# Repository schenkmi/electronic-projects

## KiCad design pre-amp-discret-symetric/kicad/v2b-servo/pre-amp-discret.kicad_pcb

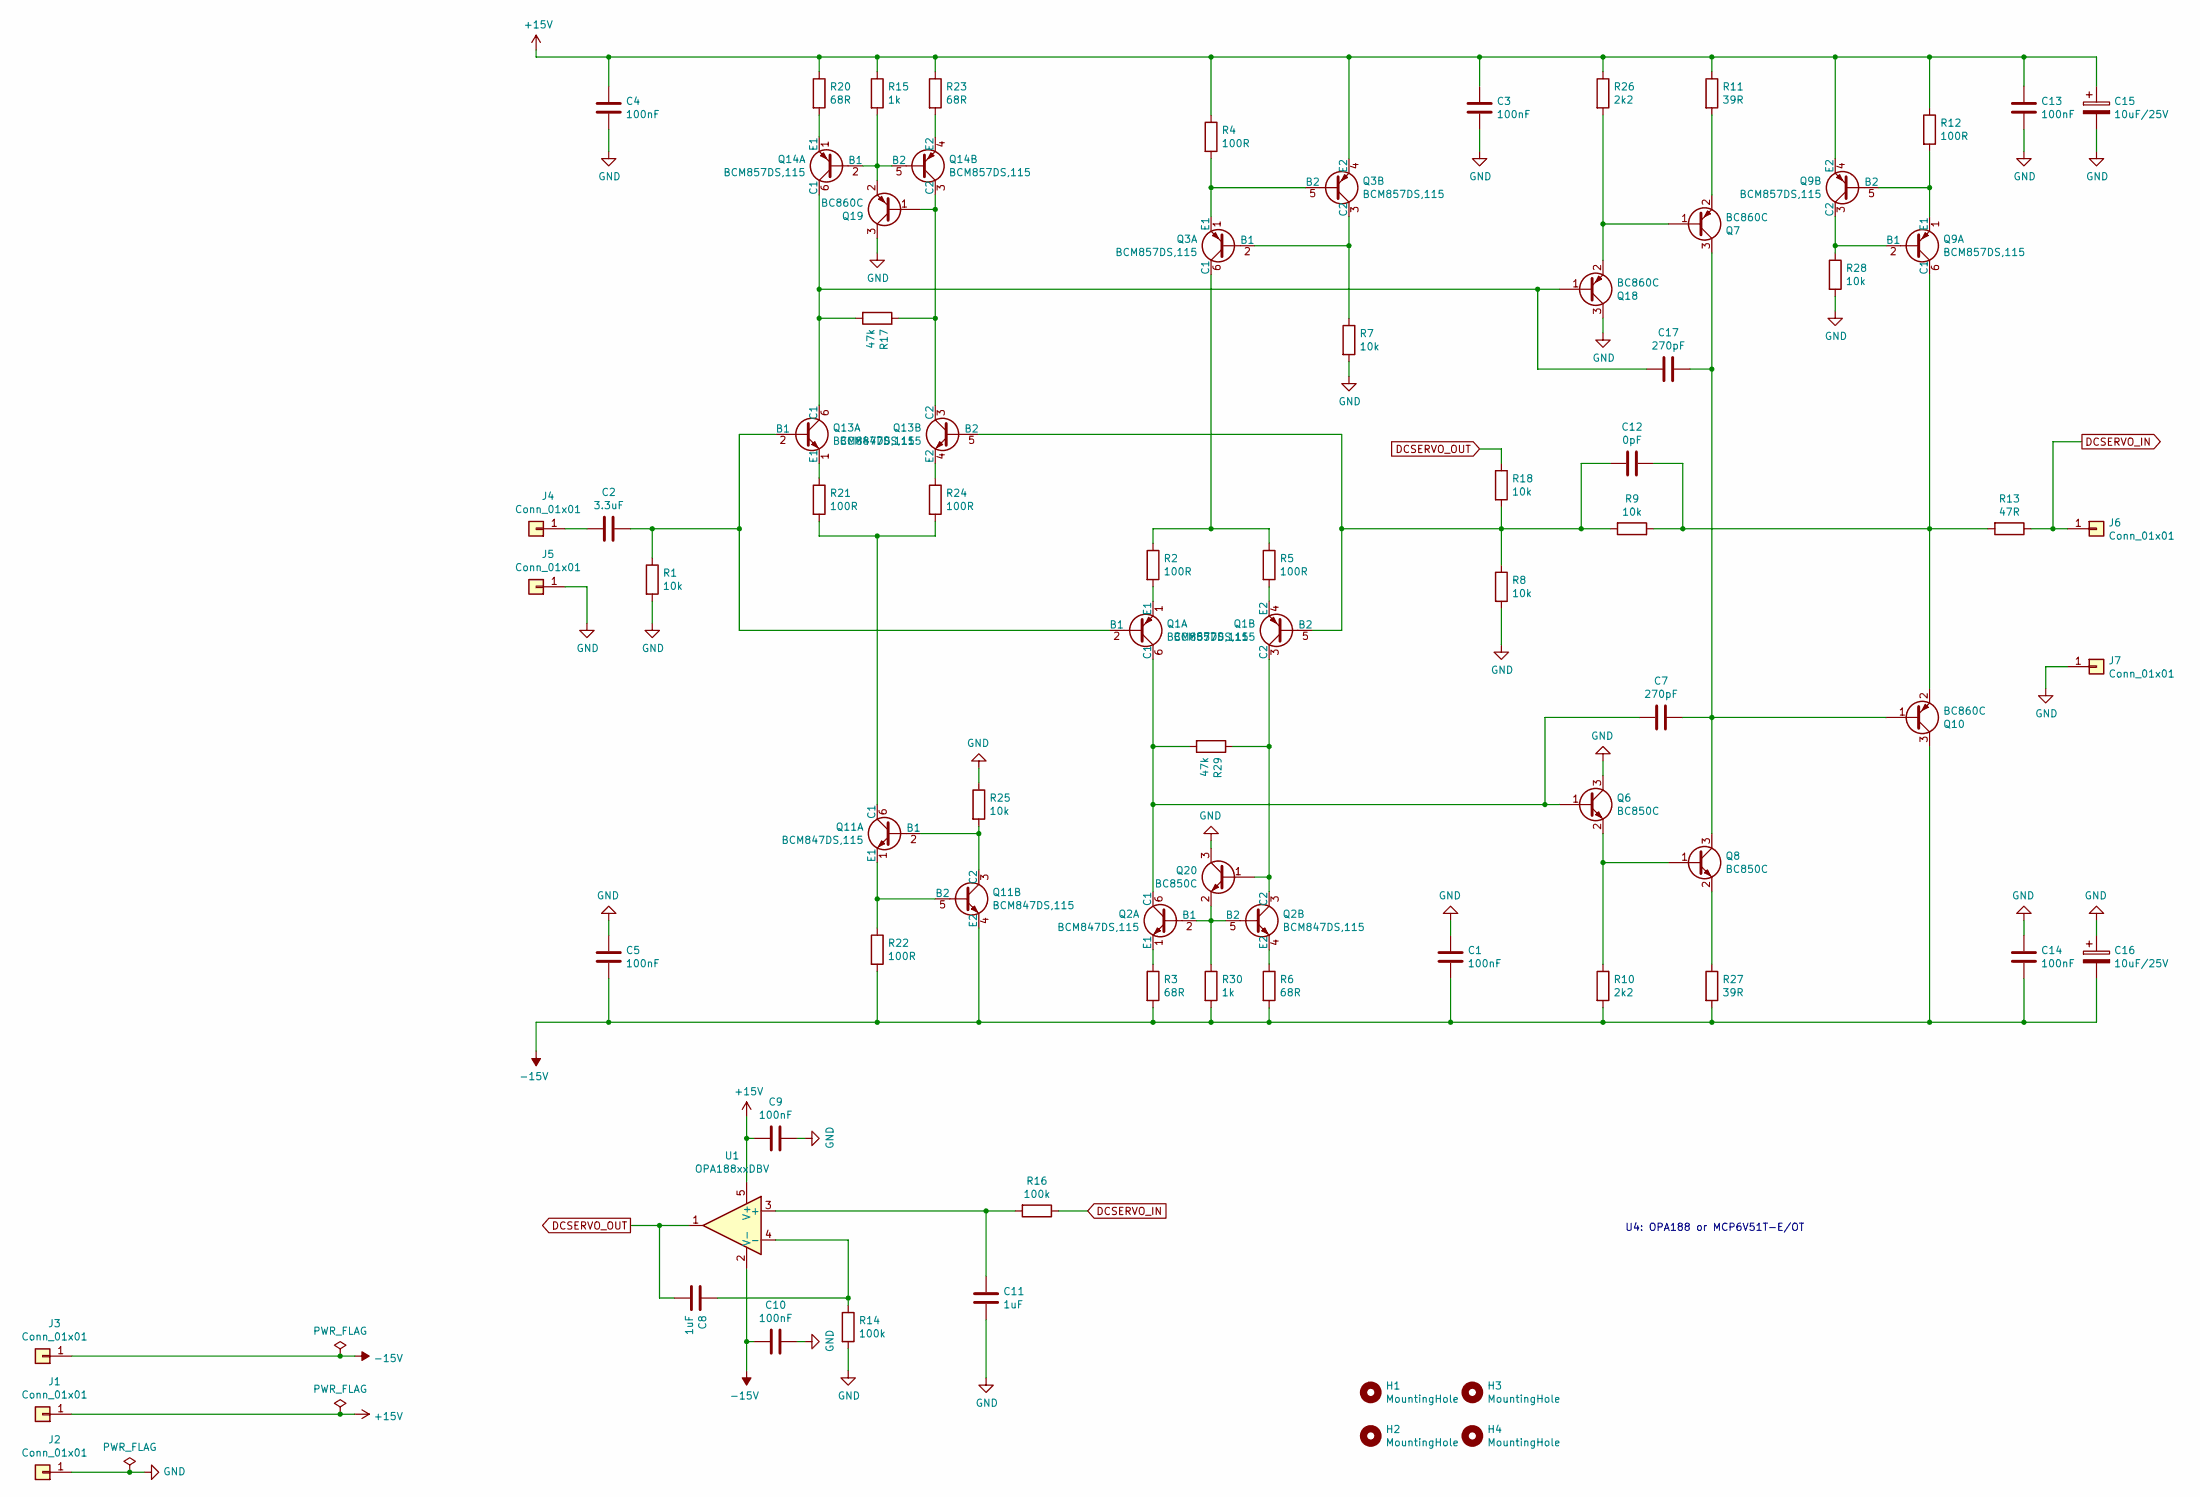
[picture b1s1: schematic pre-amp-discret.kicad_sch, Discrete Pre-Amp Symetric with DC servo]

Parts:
C1, C3, C4, C5, C13, C14: 100nF; C_1210_3225Metric_Pad1.33x2.70mm_HandSolder
C2: 3.3uF; C_Rect_L7.2mm_W7.2mm_P5.00mm_FKS2_FKP2_MKS2_MKP2
C7, C17: 270pF; C_0805_2012Metric_Pad1.18x1.45mm_HandSolder
C8, C11: 1uF; C_1210_3225Metric_Pad1.33x2.70mm_HandSolder
C9, C10: 100nF; C_0603_1608Metric_Pad1.08x0.95mm_HandSolder
C12: 0pF; C_0805_2012Metric_Pad1.18x1.45mm_HandSolder
C15, C16: 10uF/25V; CP_Elec_6.3x5.8
H1, H2, H3, H4: MountingHole; MountingHole_3.2mm_M3
J1, J2, J3, J4, J5, J6, J7: Conn_01x01; Pin_D1.0mm_L10.0mm
Q1, Q3, Q9, Q14: BCM857DS,115; SC-74-6_1.5x2.9mm_P0.95mm
Q2, Q11, Q13: BCM847DS,115; SC-74-6_1.5x2.9mm_P0.95mm
Q6, Q8, Q20: BC850C; SOT-23
Q7, Q10, Q18, Q19: BC860C; SOT-23
R1, R7, R8, R9, R18, R25, R28: 10k; R_0805_2012Metric_Pad1.20x1.40mm_HandSolder
R2, R4, R5, R12, R21, R22, R24: 100R; R_0805_2012Metric_Pad1.20x1.40mm_HandSolder
R3, R6, R20, R23: 68R; R_0805_2012Metric_Pad1.20x1.40mm_HandSolder
R10, R26: 2k2; R_0805_2012Metric_Pad1.20x1.40mm_HandSolder
R11, R27: 39R; R_0805_2012Metric_Pad1.20x1.40mm_HandSolder
R13: 47R; R_0805_2012Metric_Pad1.20x1.40mm_HandSolder
R14, R16: 100k; R_0805_2012Metric_Pad1.20x1.40mm_HandSolder
R15, R30: 1k; R_0805_2012Metric_Pad1.20x1.40mm_HandSolder
R17, R29: 47k; R_0805_2012Metric_Pad1.20x1.40mm_HandSolder
U1: OPA188xxDBV; TSOT-23-5

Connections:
+15V: C3.2, C4.2, C9.2, C13.2, C15.1, J1.1, Q3.4 (E2), Q9.4 (E2), R4.1, R11.1, R12.1, R15.1, R20.1, R23.1, R26.1, U1.5 (V+)
-15V: C1.1, C5.1, C10.2, C14.1, C16.2, J3.1, Q10.3 (C), Q11.4 (E2), R3.2, R6.2, R10.2, R22.2, R27.2, R30.2, U1.2 (V-)
DCSERVO_IN: J6.1, R13.1, R16.1
DCSERVO_OUT: C8.1, R18.1, U1.1
GND: C1.2, C3.1, C4.1, C5.2, C9.1, C10.1, C11.1, C13.1, C14.2, C15.2, C16.1, J2.1, J5.1, J7.1, Q6.3 (C), Q18.3 (C), Q19.3 (C), Q20.3 (C), R1.2, R7.2, R8.2, R14.2, R25.1, R28.2
unnamed: C2.1, Q1.2 (B1), Q13.2 (B1), R1.1
unnamed: C2.2, J4.1
unnamed: C7.2, Q1.6 (C1), Q2.6 (C1), Q6.1 (B), R29.2
unnamed: C8.2, R14.1, U1.4 (-)
unnamed: C11.2, R16.2, U1.3 (+)
unnamed: C12.1, Q9.6 (C1), Q10.2 (E), R9.1, R13.2
unnamed: C12.2, Q1.5 (B2), Q13.5 (B2), R8.1, R9.2, R18.2
unnamed: C7.1, C17.1, Q7.3 (C), Q8.3 (C), Q10.1 (B)
unnamed: C17.2, Q13.6 (C1), Q14.6 (C1), Q18.1 (B), R17.2
unnamed: Q1.1 (E1), R2.2
unnamed: Q1.3 (C2), Q2.3 (C2), Q20.1 (B), R29.1
unnamed: Q1.4 (E2), R5.2
unnamed: Q2.1 (E1), R3.1
unnamed: Q2.2 (B1), Q2.5 (B2), Q20.2 (E), R30.1
unnamed: Q2.4 (E2), R6.1
unnamed: Q3.1 (E1), Q3.5 (B2), R4.2
unnamed: Q3.2 (B1), Q3.3 (C2), R7.1
unnamed: Q3.6 (C1), R2.1, R5.1
unnamed: Q6.2 (E), Q8.1 (B), R10.1
unnamed: Q7.2 (E), R11.2
unnamed: Q8.2 (E), R27.1
unnamed: Q9.1 (E1), Q9.5 (B2), R12.2
unnamed: Q9.2 (B1), Q9.3 (C2), R28.1
unnamed: Q11.1 (E1), Q11.5 (B2), R22.1
unnamed: Q11.2 (B1), Q11.3 (C2), R25.2
unnamed: Q11.6 (C1), R21.2, R24.2
unnamed: Q13.1 (E1), R21.1
unnamed: Q13.3 (C2), Q14.3 (C2), Q19.1 (B), R17.1
unnamed: Q13.4 (E2), R24.1
unnamed: Q14.1 (E1), R20.2
unnamed: Q14.2 (B1), Q14.5 (B2), Q19.2 (E), R15.2
unnamed: Q14.4 (E2), R23.2
unnamed: Q7.1 (B), Q18.2 (E), R26.2

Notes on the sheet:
U4: OPA188 or MCP6V51T-E/OT

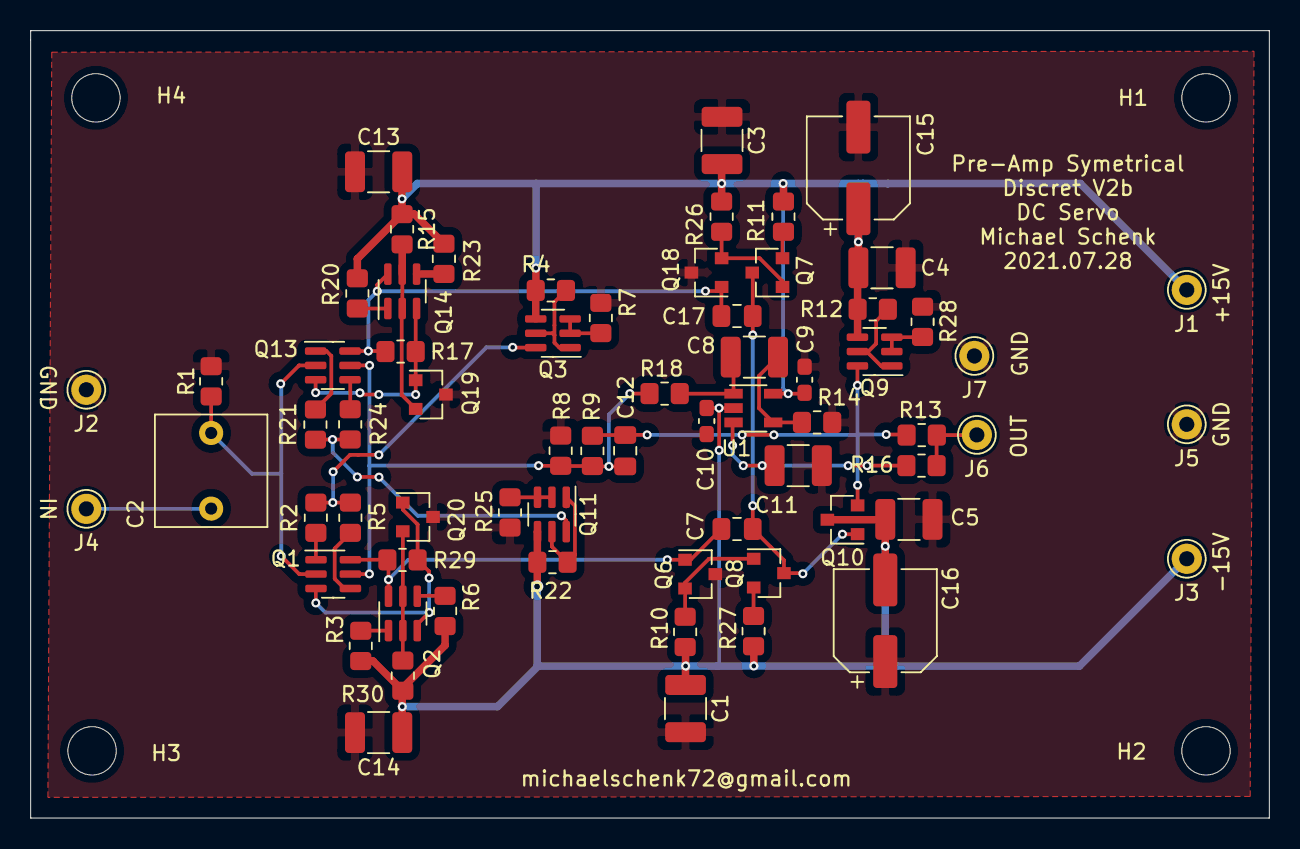
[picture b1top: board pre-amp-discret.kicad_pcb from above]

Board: 2 copper layers, 81.9 x 52.1 mm, 71 parts (0 on the bottom side), 38 nets.

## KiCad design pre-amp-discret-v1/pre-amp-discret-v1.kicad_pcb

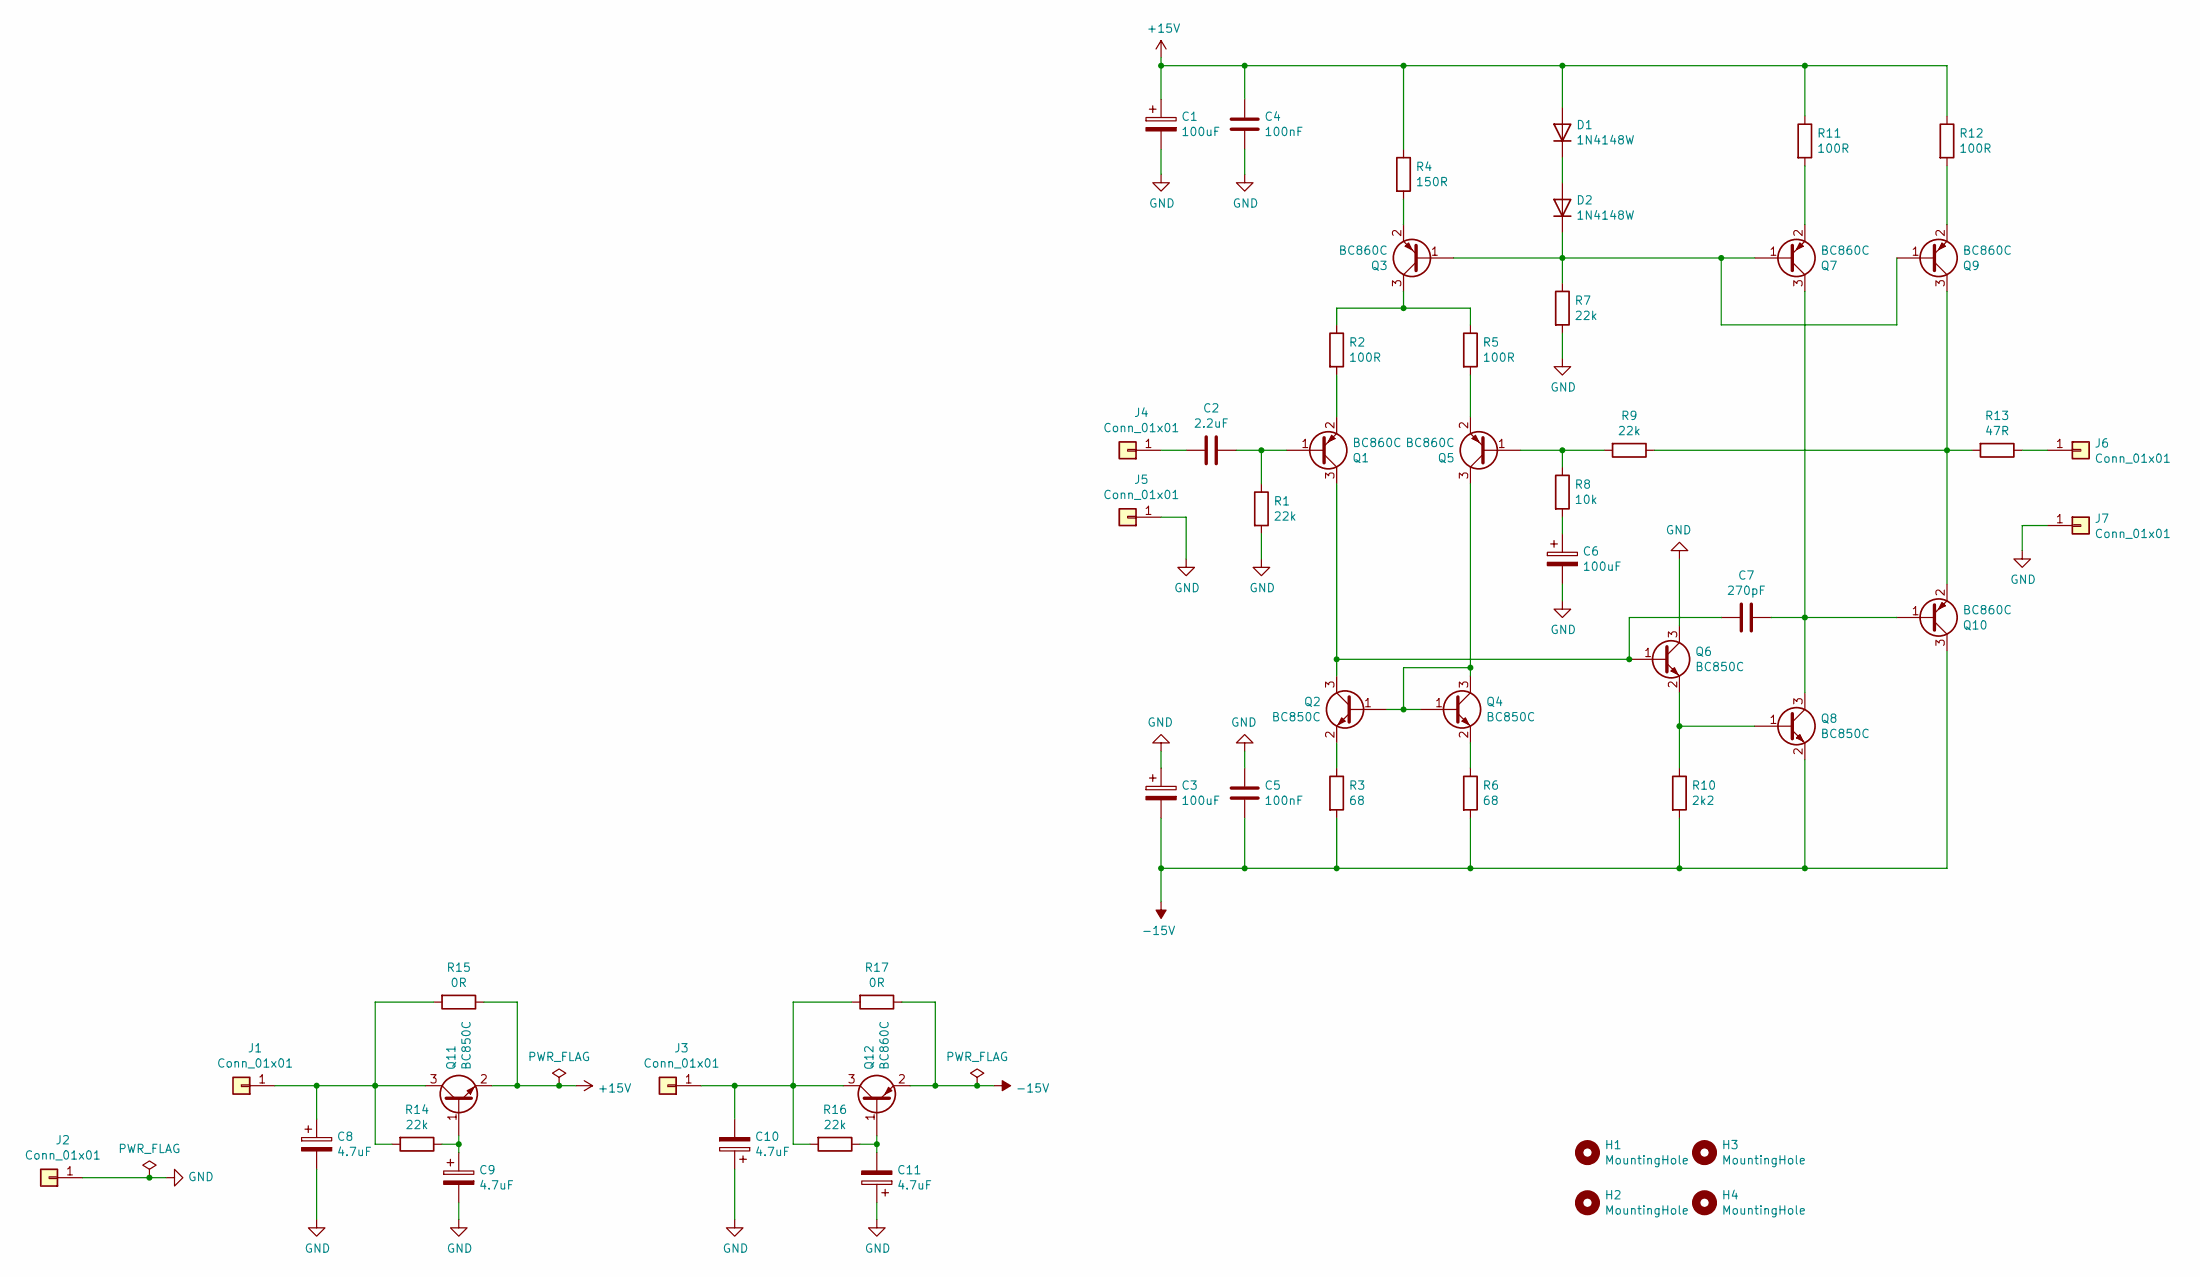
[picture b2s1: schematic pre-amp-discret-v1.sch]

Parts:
C1, C3, C6: 100uF; CP_Radial_D8.0mm_P3.50mm
C2: 2.2uF; C_Rect_L7.2mm_W7.2mm_P5.00mm_FKS2_FKP2_MKS2_MKP2
C4, C5: 100nF; C_Rect_L7.2mm_W2.5mm_P5.00mm_FKS2_FKP2_MKS2_MKP2
C7: 270pF; C_Disc_D7.0mm_W2.5mm_P5.00mm
C8, C9, C10, C11: 4.7uF; CP_Radial_D5.0mm_P2.00mm
D1, D2: 1N4148W; D_SOD-123
H1, H2, H3, H4: MountingHole; MountingHole_3.2mm_M3
J1, J2, J3, J4, J5, J6, J7: Conn_01x01; Pin_D1.3mm_L11.0mm
Q1, Q3, Q5, Q7, Q9, Q10, Q12: BC860C; SOT-23
Q2, Q4, Q6, Q8, Q11: BC850C; SOT-23
R1, R7, R9, R14, R16: 22k; R_0805_2012Metric_Pad1.20x1.40mm_HandSolder
R2, R5, R11, R12: 100R; R_0805_2012Metric_Pad1.20x1.40mm_HandSolder
R3, R6: 68; R_0805_2012Metric_Pad1.20x1.40mm_HandSolder
R4: 150R; R_0805_2012Metric_Pad1.20x1.40mm_HandSolder
R8: 10k; R_0805_2012Metric_Pad1.20x1.40mm_HandSolder
R10: 2k2; R_0805_2012Metric_Pad1.20x1.40mm_HandSolder
R13: 47R; R_0805_2012Metric_Pad1.20x1.40mm_HandSolder
R15, R17: 0R; R_Axial_DIN0204_L3.6mm_D1.6mm_P7.62mm_Horizontal

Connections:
+15V: C1.1, C4.2, D1.2 (A), Q11.2 (E), R4.1, R11.1, R12.1, R15.1
-15V: C3.2, C5.1, Q8.2 (E), Q10.3 (C), Q12.2 (E), R3.2, R6.2, R10.2, R17.1
GND: C1.2, C3.1, C4.1, C5.2, C6.2, C8.2, C9.2, C10.1, C11.1, J2.1, J5.1, J7.1, Q6.3 (C), R1.2, R7.2
unnamed: C2.1, Q1.1 (B), R1.1
unnamed: C2.2, J4.1
unnamed: C6.1, R8.2
unnamed: C7.1, Q7.3 (C), Q8.3 (C), Q10.1 (B)
unnamed: C7.2, Q1.3 (C), Q2.3 (C), Q6.1 (B)
unnamed: C8.1, J1.1, Q11.3 (C), R14.2, R15.2
unnamed: C9.1, Q11.1 (B), R14.1
unnamed: C10.2, J3.1, Q12.3 (C), R16.2, R17.2
unnamed: C11.2, Q12.1 (B), R16.1
unnamed: D1.1 (K), D2.2 (A)
unnamed: D2.1 (K), Q3.1 (B), Q7.1 (B), Q9.1 (B), R7.1
unnamed: J6.1, R13.1
unnamed: Q1.2 (E), R2.2
unnamed: Q2.1 (B), Q4.1 (B), Q4.3 (C), Q5.3 (C)
unnamed: Q2.2 (E), R3.1
unnamed: Q3.2 (E), R4.2
unnamed: Q3.3 (C), R2.1, R5.1
unnamed: Q4.2 (E), R6.1
unnamed: Q5.1 (B), R8.1, R9.2
unnamed: Q5.2 (E), R5.2
unnamed: Q6.2 (E), Q8.1 (B), R10.1
unnamed: Q7.2 (E), R11.2
unnamed: Q9.2 (E), R12.2
unnamed: Q9.3 (C), Q10.2 (E), R9.1, R13.2

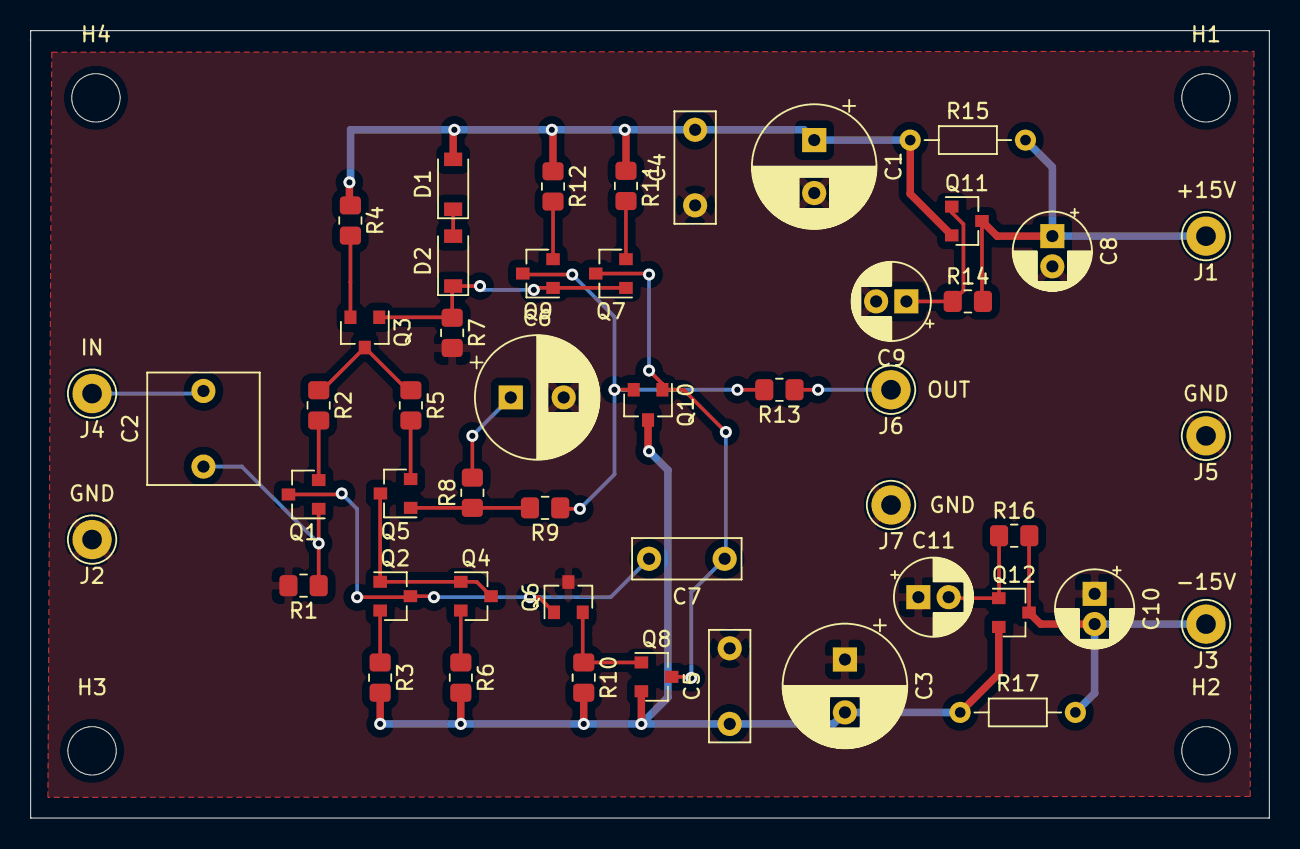
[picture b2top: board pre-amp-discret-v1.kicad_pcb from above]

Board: 2 copper layers, 81.9 x 52.1 mm, 53 parts (0 on the bottom side), 27 nets.
